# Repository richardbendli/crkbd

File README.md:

# Corne keyboard

The Corne keyboard is a split keyboard with 3x6 column staggered keys
and 3 thumb keys, based on [Helix](https://github.com/MakotoKurauchi/helix).
Crkbd stands for Corne Keyboard.

# Build Guide

This is the build guide for Corne Chocolate.

## Parts

### Required

| Name | Count | Remarks |
|:-|:-|:-|
| PCB | 2 pieces | |
| Top plate | 2 pieces | |
| Bottom plate | Two pieces | PCB type and acrylic type are available |
| Pro Micro protection plate | 2 pieces | |
| Pro Micro | 2 | |
| TRRS Jack | 2 | |
| Tactile switch | 2 pieces | |
| Diode | 42 pieces | Compatible with chip components only
| Kailh PCB Socket (for Choc) | 42 | |
| Key switch | 42 pieces | Compatible with Choc (low profile) only |
| Key-caps | 42 | 1u 40, 1.5u 2 |
| OLED module | 2 pieces | |
| 4 pin headers | 2 | |
| 4 pin sockets | 2 | |
| Spacer M2 4.5mm | 10 | |
| Spacer M2 9mm | Four | |
| Screw M2 4mm | 28 | |
| Cushion rubber | 8 pieces | |
| TRS (3 pole) cable | 1 | TRRS (4 pole) cable also available |
| Micro USB Cable | 1 | |

### Optional

| Name | Count | Remarks |
|:-|:-|:-|
| SK6812MINI | 54 | 42 for backlight, 12 for under-glow |

## Advance preparation

If you build the firmware yourself,
it will take some time to set up the environment,
so it's best to start at the beginning. \
For more information,
please see <https://github.com/foostan/crkbd/blob/master/doc/firmware_en.md>.

## Building

Since the PCB is reversible,
you first have to decide which one to use for the left side.

### Diodes

Solder the diodes to the PCB.

On Corne Cherry, it is up to you to choose which side to attach,
but with Corne Chocolate you must **be sure to attach it to the back**.
Mounting on the front will interfere with the top plate.

Since the diodes are very small,
it is easier to work with tweezers and inverted tweezers.
Since the **mounting orientation of the diode is crucial**,
it is possible to proceed smoothly
if you arrange the columns and rows to be mounted in advance,
as shown in the following photo.

The orientation of the diode is as follows.
Attach the chip component so that the "|||" mark on the diode is facing the "|"
of the diode mark "|◁" on the PCB (image from Corne Cherry).

Tip for soldering on SMD parts:
First put solder only on the right side of the pad.

Next, solder one of the diodes by melting the solder you already put on the board.
At this time,
it is recommended to use a reverse-action tweezers,
so that you can hold the SMD part firmly without applying force,
and concentrate on alignment and soldering instead.
Also, if the soldering iron is too hot or the solder is touched too long,
the flux contained in the solder may evaporate and form an undesirable pile solder,
but since it can be repaired later,
so at this point you should only care about attaching parts.
It's okay.

Then solder the other pin.
Be careful not to apply too much solder,
as a small amount is sufficient.
If you have applied too much,
you can remove it with a suction pump, blotting wire
or by scooping it with a soldering iron.

If the amount of solder on the pre-soldering side is too small,
add more soldering,
and if it is pilled up,
apply flux from above and heat to clean.

### TRRS jack, reset switch, pin socket

Solder the TRRS jack, reset switch and pin socket to the **front of the PCB**
as shown in the picture below.
Since the diode is attached on the back side,
it will be on the opposite side.

### Jumpers for OLED modules

When using an OLED module, use solder as jumpers (4 times per side) as follows.
**Please jumper only on the surface**.

If the jumper doesn't work,
you probably have a small amount of solder,
or the flux has vaporized.
If so, you can fix the jumper by applying more solder or separate flux.

### Pro Micro

Solder the pin headers to the white frame
and solder the Pro Micro with back side up.

When using the spring-loaded pin headers,
please refer to the [Helix Build Guide](
https://github.com/MakotoKurauchi/helix/blob/master/Doc/buildguide_en.md#pro-micro).

### OLED module

Insert the pin header into the OLED pin socket first,
then solder the pin header and the OLED module.
At this time,
make sure that the OLED module sits tightly on the socket
while holding it down with your finger,
because it tends to stick out easily.

### Operation check

We recommend that you check the operation at the stage
where the Pro Micro and OLED modules are attached
(it is difficult to isolate the problem at the end).

Before checking the correct operation,
flash the crkbd firmware to the Pro Micro
by referring to the [Firmware](#firmware) section below
(be sure to insert it on both sides).

Operation confirmation is performed
by connecting the left hand side to a PC with Micro USB
and connecting the left hand side and the right hand side with a TRS cable.
Since there may be a defect such as a jack,
make sure to connect the left and right
instead of one by one before checking the operation.
If you have done this correctly,
short-circuit the pad to attach the PCB socket with tweezers,
and the key pressed on the OLED module will be displayed.

## LED (optional)

I will install SK6812MINI.
The LED can be mounted even after completion,
so if you are worried about mounting it,
we recommend that you skip this chapter and complete it first.

SK6812MINI is very heat sensitive and breaks easily.
We recommend using a soldering iron with a temperature control function
and operating at a temperature of about 220°C to 270°C.
Even if the temperature is set that low,
the LED will be damaged if the iron is left on it for a long time,
so try to solder as quickly as possible.
Solder four LEDs at a time,
but we recommend soldering two at a time instead of four at a time
to prevent the LED temperature from rising,
as this will make it less likely to overheat.

First, check the mounting position.

Solder 1 - 6 so that the back side (under-glow) shines,
7 - 27 so that the front side (back-light) shines.
Below is the location to attach the LED (image from Corne Cherry).

For LEDs 1 to 6,
solder the part so that the black part circled below is on the bottom
and the silk mark indicated by the arrow is on the top.
Note that the direction changes between 1 - 3 and 4 - 5.

For 7 - 27,
perform soldering so that the largest pad surrounded by a circle
and the silk mark indicated by an arrow are adjacent to each other,
as shown below.

If everything was successfully soldered,
it will glow as follows.
If the LED lights only halfway,
the LEDs are connected in the order of the numbers.
Therefore, it is likely that the LED that does not emit light
or the previous LED are incorrectly soldered or damaged.

### Kailh PCB Socket

Apply solder to the pads on both sides on the back.
It is difficult to add it later,
so please fill it up beforehand.

Insert the socket and melt the solder.
At this time,
hold the socket with tweezers or your fingers so that the socket sticks to the board.

The soldering is now complete.

### Plate, switch

Use 4.5mm spacers for the top and bottom plates
and 9mm spacers for the OLED.

In addition,
it is recommended to paint the side of the plate with a black marker
because it looks better.

## Firmware

See below to flash the firmware to the ProMicro. \
<https://github.com/foostan/crkbd/blob/master/doc/firmware_en.md>

This is the end.

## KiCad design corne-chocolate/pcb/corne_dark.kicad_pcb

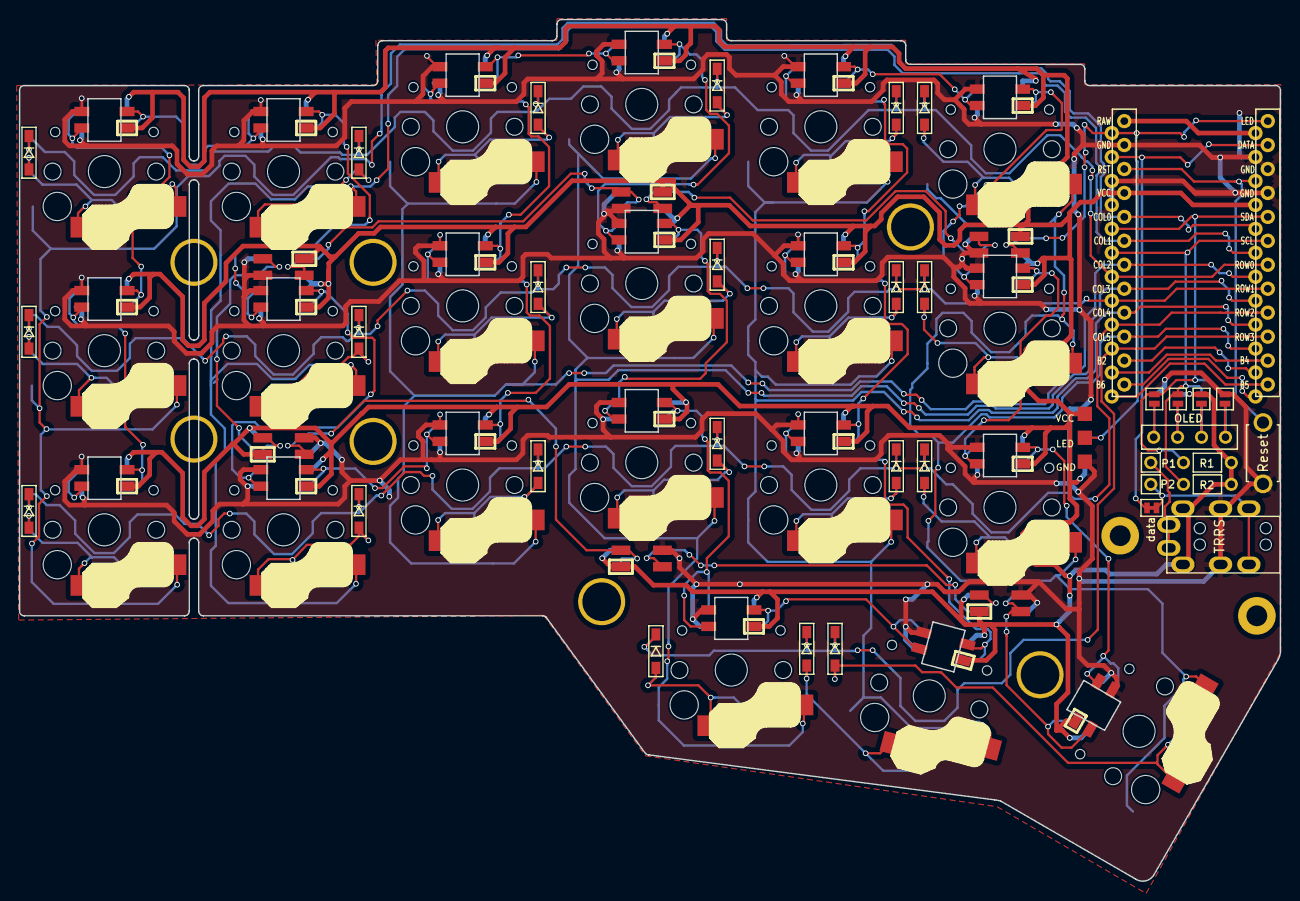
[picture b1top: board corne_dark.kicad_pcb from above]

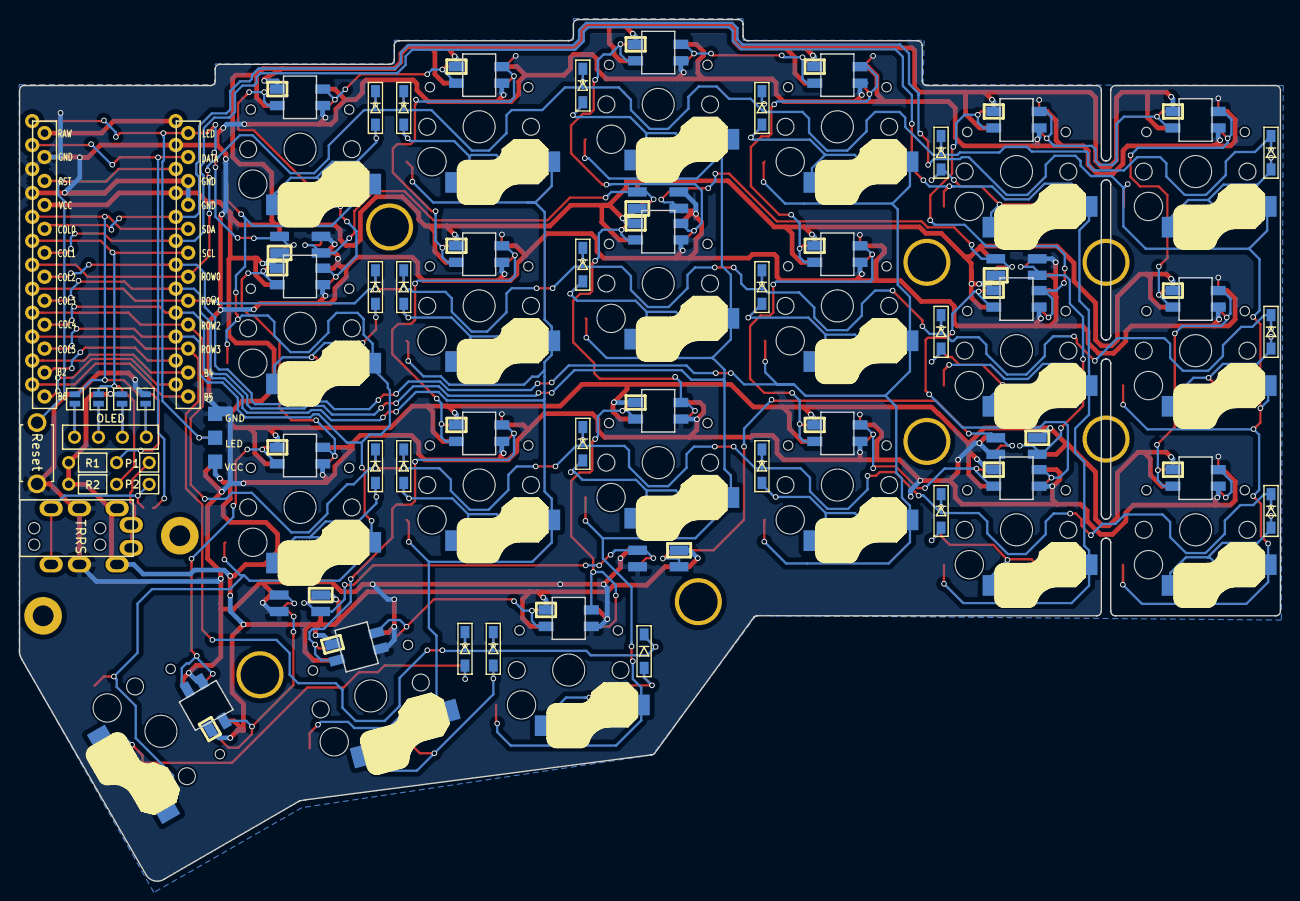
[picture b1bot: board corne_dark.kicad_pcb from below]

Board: 2 copper layers, 133.8 x 91.4 mm, 87 parts (4 on the bottom side), 70 nets.

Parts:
D1, D2, D3, D4, D5, D6, D7, D8, D9, D10, D11, D12, D13, D14, D15, D16, D17, D18, D19, D20, D21: D; D3_SMD
J3: LED; StripLED_rev
JP2, JP3, JP4, JP5, JP6, JP7, JP8, JP9: Jumper
L1, L2, L3, L4, L5, L6, L7, L8, L9, L10, L11, L12, L13, L14, L15, L16, L17, L18, L19, L20, L21: SK6812MINI; SK6812MINI_rev
L22, L23, L24, L25, L26, L27: SK6812MINI; SK6812MINI_underglow_rev
OLED: OLED
P1, P2: i2c-pin; 1pin_conn
R1, R2: R
RSW1: Reset; ResetSW
SW1, SW2, SW3, SW4, SW5, SW6, SW7, SW8, SW9, SW10, SW11, SW12, SW13, SW14, SW15, SW16, SW17, SW18, SW19, SW20: SW_PUSH; Choc_Hotswap
SW21: SW_PUSH; Choc_Hotswap_1.5u
TRRS: MJ-4PP-9
U1: ProMicro; ProMicro_v2
data: JPC2

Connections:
GND: J3.1, JP2.1, JP9.1, L1.2, L2.2, L3.2, L4.2, L5.2, L6.2, L7.2, L8.2, L9.2, L10.2, L11.2, L12.2, L13.2, L14.2, L15.2, L16.2, L17.2, L18.2, L19.2, L20.2, L21.2, L22.2, L23.2, L24.2, L25.2, L26.2, L27.2, RSW1.2, TRRS.C, U1.3, U1.4, U1.23
LED: J3.2, L24.3, U1.1
unnamed: D1.2, SW1.2
unnamed: D2.2, SW2.2
unnamed: D3.2, SW3.2
unnamed: D4.2, SW4.2
unnamed: D5.2, SW5.2
unnamed: D6.2, SW6.2
unnamed: D7.2, SW7.2
unnamed: D8.2, SW8.2
unnamed: D9.2, SW9.2
unnamed: D10.2, SW10.2
unnamed: D11.2, SW11.2
unnamed: D12.2, SW12.2
unnamed: D13.2, SW13.2
unnamed: D14.2, SW14.2
unnamed: D15.2, SW15.2
unnamed: D16.2, SW16.2
unnamed: D17.2, SW17.2
unnamed: D18.2, SW18.2
unnamed: D19.2, SW19.2
unnamed: D20.2, SW20.2
unnamed: D21.2, SW21.2
unnamed: P1.1, TRRS.A
unnamed: P2.1, TRRS.B, data.2
unnamed: JP5.2, JP9.2, OLED.1
unnamed: JP4.2, JP8.2, OLED.2
unnamed: JP3.2, JP7.2, OLED.3
unnamed: JP2.2, JP6.2, OLED.4
unnamed: L1.1, L7.3
unnamed: L1.3, L2.1
unnamed: L2.3, L8.1
unnamed: L3.1, L9.3
unnamed: L3.3, L4.1
unnamed: L5.3, L6.1
unnamed: L4.3, L10.1
unnamed: L10.3, L16.1
unnamed: L11.1, L17.3
unnamed: L5.1, L11.3
unnamed: L6.3, L12.1
unnamed: L12.3, L18.1
unnamed: L7.1, L13.3
unnamed: L8.3, L14.1
unnamed: L14.3, L15.1
unnamed: L9.1, L15.3
unnamed: L16.3, L19.1
unnamed: L17.1, L20.3
unnamed: L18.3, L21.1
unnamed: L19.3, L20.1
unnamed: L21.3, L27.1
unnamed: L22.1, L25.3
unnamed: L22.3, L23.1
unnamed: L23.3, L24.1
unnamed: L25.1, L26.3
unnamed: L26.1, L27.3
SCL: JP4.1, JP7.1, R2.2, U1.6
SDA: JP5.1, JP6.1, R1.2, U1.5
VCC: J3.3, JP3.1, JP8.1, L1.4, L2.4, L3.4, L4.4, L5.4, L6.4, L7.4, L8.4, L9.4, L10.4, L11.4, L12.4, L13.4, L14.4, L15.4, L16.4, L17.4, L18.4, L19.4, L20.4, L21.4, L22.4, L23.4, L24.4, L25.4, L26.4, L27.4, R1.1, R2.1, TRRS.D, U1.21
col0: SW1.1, SW7.1, SW13.1, U1.20
col1: SW2.1, SW8.1, SW14.1, U1.19
col2: SW3.1, SW9.1, SW15.1, U1.18
col3: SW4.1, SW10.1, SW16.1, SW19.1, U1.17
col4: SW5.1, SW11.1, SW17.1, SW20.1, U1.16
col5: SW6.1, SW12.1, SW18.1, SW21.1, U1.15
data: U1.2, data.1
reset: RSW1.1, U1.22
row0: D1.1, D2.1, D3.1, D4.1, D5.1, D6.1, U1.7
row1: D7.1, D8.1, D9.1, D10.1, D11.1, D12.1, U1.8
row2: D13.1, D14.1, D15.1, D16.1, D17.1, D18.1, U1.9
row3: D19.1, D20.1, D21.1, U1.10

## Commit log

2023-09-27 corne keyboard
2023-10-14 crkbd build
2023-10-28 build guide
2023-11-22 remove gcode
2023-11-26 rename stl
